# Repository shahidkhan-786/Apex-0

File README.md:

# Apex-0

Hello
This Readme is a detailed guide or can say walkthrough of my RC plane making journey.

Apex 0 is a RC trainer plane with 4 control channels.
Made with custom transmitter and reciever.
It will have four controls (Throttle, Ailerons, Rudder and Elevator) 
I will be using ESP32 along with ELRS for communication and controlling servos and throttle.

I am referring to this video : https://youtu.be/LzZ4Oqk_J1Y?si=26B0NShiXBWvZHp2
for structure part...but there was a flaw...The flight time...I have optimized the design for longer flight time.

Also I will be making my own remote controller with 2 Joystick modules.

Since I was little I was amazed by people flying planes and drones, basically all flying stuff. and thats why I wanna make my own plane.

Note that for the first iteration I will be making reciever on a perfboard/zero PCB ...and hence there is no pcb in 3D model.
Reviewers please do not overlook it.

so for the dimensions and proportions you can see my blueprints part where I have showed exact dimensions I will be using.

and for the 3D model you can see my 3D section.

Now for the electronics part :

The transmitter Circuit and PCB : 

and now the reciever part, again note that I am making this on a perfboard and hence there is no layout/routing part :

The BOM screenshots : 

Cart Screenshot (I am ordering froma website called Robu.in) :

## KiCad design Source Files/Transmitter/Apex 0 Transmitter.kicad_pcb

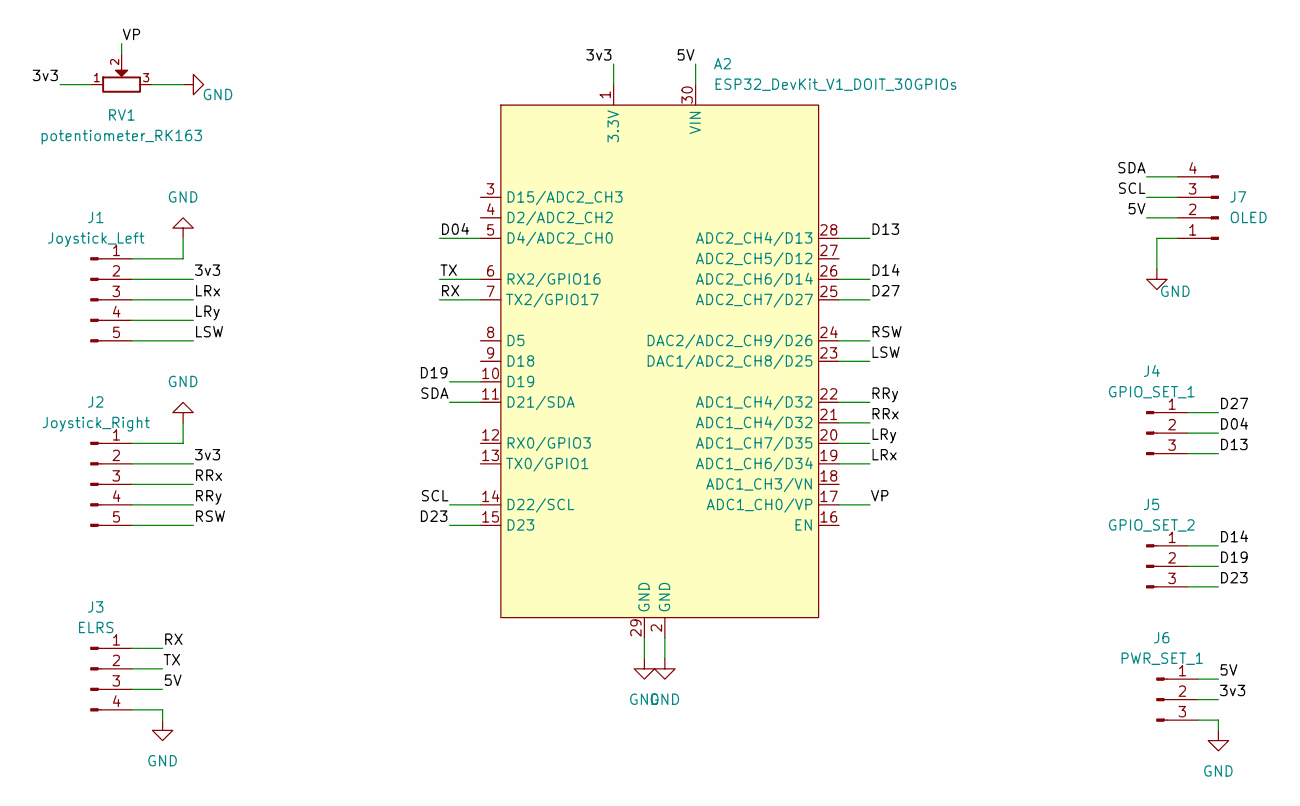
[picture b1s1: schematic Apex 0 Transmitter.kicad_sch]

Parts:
A2: ESP32_DevKit_V1_DOIT_30GPIOs; DOIT_ESP32_DEVKIT_30Pins
J1: Joystick_Left; PinHeader_1x05_P2.54mm_Vertical
J2: Joystick_Right; PinHeader_1x05_P2.54mm_Vertical
J3: ELRS; PinHeader_1x04_P2.54mm_Vertical
J4: GPIO_SET_1; PinHeader_1x03_P2.54mm_Vertical
J5: GPIO_SET_2; PinHeader_1x03_P2.54mm_Vertical
J6: PWR_SET_1; PinHeader_1x03_P2.54mm_Vertical
J7: OLED; PinHeader_1x04_P2.54mm_Vertical
RV1: potentiometer_RK163; Potentiometer_Alps_RK163_Single_Horizontal

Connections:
/3v3: A2.1 (3.3V), J1.2, J2.2, J6.2, RV1.1
/5V: A2.30 (VIN), J3.3, J6.1, J7.2
/D04: A2.5 (D4/ADC2_CH0), J4.2
/D13: A2.28 (ADC2_CH4/D13), J4.3
/D14: A2.26 (ADC2_CH6/D14), J5.1
/D19: A2.10 (D19), J5.2
/D23: A2.15 (D23), J5.3
/D27: A2.25 (ADC2_CH7/D27), J4.1
/LRx: A2.19 (ADC1_CH6/D34), J1.3
/LRy: A2.20 (ADC1_CH7/D35), J1.4
/LSW: A2.23 (DAC1/ADC2_CH8/D25), J1.5
/RRx: A2.21 (ADC1_CH4/D32), J2.3
/RRy: A2.22 (ADC1_CH4/D32), J2.4
/RSW: A2.24 (DAC2/ADC2_CH9/D26), J2.5
/RX: A2.7 (TX2/GPIO17), J3.1
/SCL: A2.14 (D22/SCL), J7.3
/SDA: A2.11 (D21/SDA), J7.4
/TX: A2.6 (RX2/GPIO16), J3.2
/VP: A2.17 (ADC1_CH0/VP), RV1.2
GND: A2.2 (GND), A2.29 (GND), J1.1, J2.1, J3.4, J6.3, J7.1, RV1.3

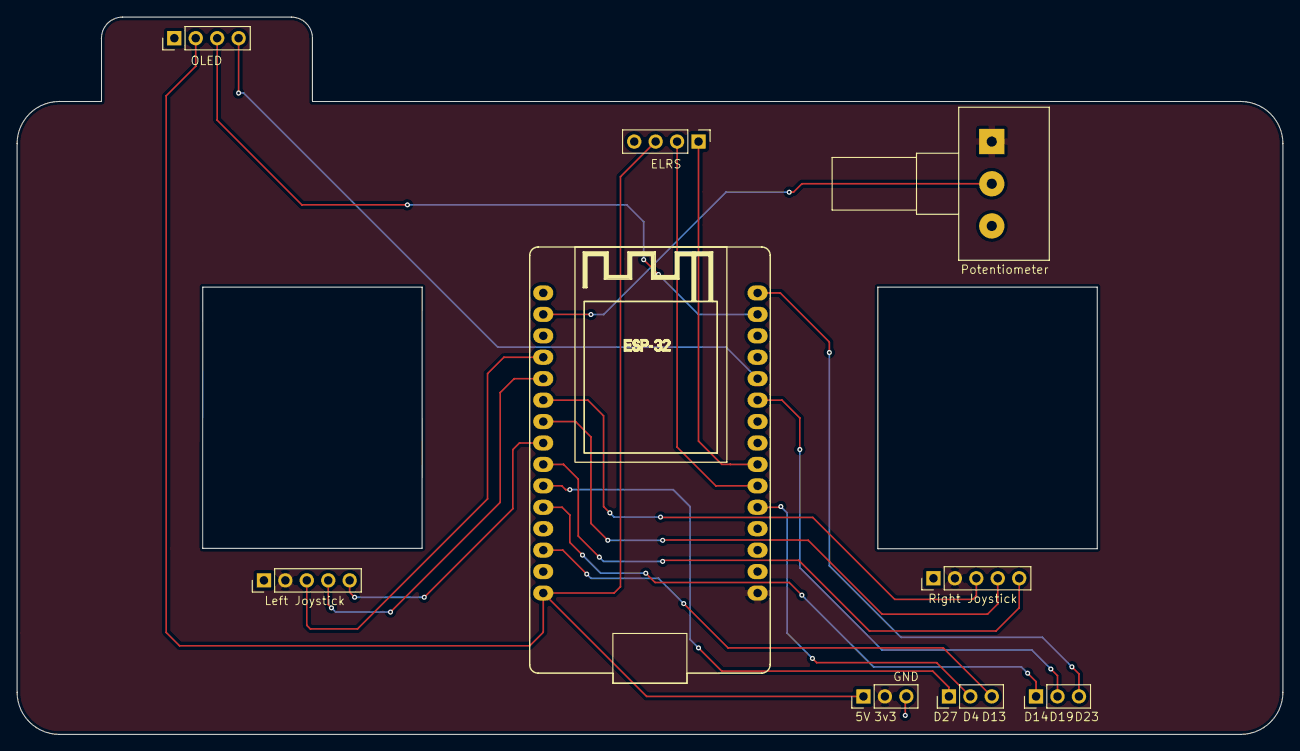
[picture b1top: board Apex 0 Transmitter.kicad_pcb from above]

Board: 2 copper layers, 150.0 x 85.0 mm, 9 parts (0 on the bottom side), 20 nets.

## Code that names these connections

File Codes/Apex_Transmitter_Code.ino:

/*
 * APEX 0 - DIY ExpressLRS Radio Transmitter Handset
 * Developed for Hack Club Macondo Project
 * * Target MCU: ESP32 30-Pin DevKit
 * Mappings perfectly matched to Final Transmitter Schematic
 */

#include <Wire.h>
#include <Adafruit_GFX.h>
#include <Adafruit_SSD1306.h>

// --- Hardware Pin Definitions ---
#define PIN_JOY_LEFT_X  34  // LRx (ADC1)
#define PIN_JOY_LEFT_Y  35  // LRy (ADC1)
#define PIN_SWITCH_LEFT 25  // LSW (Digital Input)

#define PIN_JOY_RIGHT_X 32  // RRx (ADC1)
#define PIN_JOY_RIGHT_Y 33  // RRy (ADC1)
#define PIN_SWITCH_RIGHT 26 // RSW (Digital Input)

#define PIN_POT_AUX     36  // VP (ADC1 Tuning Potentiometer)

#define PIN_UART_TX2    17  // Connected to ELRS RX Pad
#define PIN_UART_RX2    16  // Connected to ELRS TX Pad

// --- OLED Configuration ---
#define SCREEN_WIDTH 128
#define SCREEN_HEIGHT 64
Adafruit_SSD1306 display(SCREEN_WIDTH, SCREEN_HEIGHT, &Wire, -1);

// --- CRSF Frame Structures ---
#define CRSF_START_BYTE     0xC8
#define CRSF_FRAMETYPE_RC_CHANNELS 0x16

struct CrsfChannels {
    unsigned int ch0 : 11;
    unsigned int ch1 : 11;
    unsigned int ch2 : 11;
    unsigned int ch3 : 11;
    unsigned int ch4 : 11;
    unsigned int ch5 : 11;
    unsigned int ch6 : 11;
    unsigned int ch7 : 11;
    unsigned int ch8 : 11;
    unsigned int ch9 : 11;
    unsigned int ch10 : 11;
    unsigned int ch11 : 11;
    unsigned int ch12 : 11;
    unsigned int ch13 : 11;
    unsigned int ch14 : 11;
    unsigned int ch15 : 11;
} __attribute__((packed));

uint8_t crsfPacket[26];

// --- CRC8 Calculation Function for ExpressLRS ---
uint8_t crsf_crc8(const uint8_t *ptr, uint8_t len) {
    uint8_t crc = 0;
    while (len--) {
        crc ^= *ptr++;
        for (uint8_t i = 0; i < 8; i++) {
            if (crc & 0x80) {
                crc = (crc << 1) ^ 0xD5;
            } else {
                crc <<= 1;
            }
        }
    }
    return crc;
}

void setup() {
    // Initialize Debug Console
    Serial.begin(115200);
    
    // Initialize Hardware UART2 for ExpressLRS Module at native CRSF Speed
    Serial2.begin(416666, SERIAL_8N1, PIN_UART_RX2, PIN_UART_TX2);
    
    // Configure Switches with internal pullups
    pinMode(PIN_SWITCH_LEFT, INPUT_PULLUP);
    pinMode(PIN_SWITCH_RIGHT, INPUT_PULLUP);
    
    // Initialize I2C OLED Screen
    if(!display.begin(SSD1306_SWITCHCAPVCC, 0x3C)) {
        Serial.println(F("OLED allocation failed"));
    } else {
        display.clearDisplay();
        display.setTextSize(1);
        display.setTextColor(SSD1306_WHITE);
        display.setCursor(0,0);
        display.println("  APEX 0 TX ONLINE  ");
        display.println("   HACKCLUB MACONDO ");
        display.display();
    }
}

void loop() {
    // 1. Read Analog Joysticks and Pot (ESP32 12-bit ADC: 0 to 4095)
    int raw_roll     = analogRead(PIN_JOY_RIGHT_X);
    int raw_pitch    = analogRead(PIN_JOY_RIGHT_Y);
    int raw_throttle = analogRead(PIN_JOY_LEFT_Y);
    int raw_yaw      = analogRead(PIN_JOY_LEFT_X);
    int raw_aux      = analogRead(PIN_POT_AUX);
    
    // 2. Map values to standard ExpressLRS channel limits (CRSF ranges from 172 to 1811)
    // Center point is 992. Equivalent to standard 1000us - 2000us servo signals.
    uint16_t crsf_roll     = map(raw_roll,     0, 4095, 172, 1811);
    uint16_t crsf_pitch    = map(raw_pitch,    0, 4095, 172, 1811);
    uint16_t crsf_throttle = map(raw_throttle, 0, 4095, 172, 1811);
    uint16_t crsf_yaw      = map(raw_yaw,      0, 4095, 172, 1811);
    uint16_t crsf_aux      = map(raw_aux,      0, 4095, 172, 1811);
    
    uint16_t sw_l = (digitalRead(PIN_SWITCH_LEFT) == LOW) ? 1811 : 172;
    uint16_t sw_r = (digitalRead(PIN_SWITCH_RIGHT) == LOW) ? 1811 : 172;

    // 3. Assemble the CRSF Serialization Packet Array
    crsfPacket[0] = CRSF_START_BYTE;
    crsfPacket[1] = 24; // Packet Payload Length
    crsfPacket[2] = CRSF_FRAMETYPE_RC_CHANNELS;
    
    CrsfChannels *channels = (CrsfChannels *)&crsfPacket[3];
    channels->ch0 = crsf_roll;
    channels->ch1 = crsf_pitch;
    channels->ch2 = crsf_throttle;
    channels->ch3 = crsf_yaw;
    channels->ch4 = sw_l;
    channels->ch5 = sw_r;
    channels->ch6 = crsf_aux;
    
    // Calculate Checksum over payload and payload header type
    crsfPacket[25] = crsf_crc8(&crsfPacket[2], 23);
    
    // 4. Stream data frame down the serial pipeline directly to the ELRS module
    Serial2.write(crsfPacket, 26);
    
    // 5. Refresh OLED Telemetry Screen Layout at a clean 10Hz pace
    static unsigned long lastUpdate = 0;
    if (millis() - lastUpdate > 100) {
        lastUpdate = millis();
        display.clearDisplay();
        display.setCursor(0,0);
        display.println("--- APEX 0 LINK ---");
        display.printf("THR: %d\n", map(crsf_throttle, 172, 1811, 0, 100));
        display.printf("RLL: %d | PTH: %d\n", map(crsf_roll, 172, 1811, -50, 50), map(crsf_pitch, 172, 1811, -50, 50));
        display.printf("AUX POT: %d\n", map(crsf_aux, 172, 1811, 0, 100));
        display.println("STATUS: WAITING RX...");
        display.display();
    }
    
    delay(20); // Balanced 50Hz control loop interval
}

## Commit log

2026-02-22 Update README with Trainer plane project details
    Added details about the Trainer plane project and its components.
2026-02-22 Create Apex 0
2026-02-22 These are Cart Screenshots
2026-02-22 Main Blueprint
    These are the main Schematic I will be using for the build.
2026-02-22 Add files via upload
    This is screenshot of my BOM
2026-03-22 Create Apex-0
    This folder contains all 3D files and also Screenshoots required
2026-03-22 These are the 3D files required
    These are Rough (Yet most finished) models...you have to place holes according to your screw needs and also motor mounts according to your motor sizes.
    I have made the sketch in Blueprint folder where can you place motor mounts according to your motor and needs
2026-03-23 Update README with project details and image
    Added an image and additional information about the project.
2026-03-23 Update README with 3D model section and images
    Removed redundancy in the 3D model section and added additional screenshots.
2026-03-23 Update README with new images
    Added additional images to the README for better visualization.
2026-03-24 Add transmitter code for RF24 communication
2026-03-24 Add receiver code for RF24 radio and servos
2026-03-24 Add note about ESP32 version differences
2026-03-25 This is BOM for the project
2026-03-25 Update README with Bill of Materials and images
    Added Bill of Materials section and updated images.
2026-05-08 Justification for 12Hrs
    Unfortunately I can't show each and every parametric of model/sketches...but seeing the timeline you know that I have genuinely put hours in making...
2026-05-18 Revise README for Apex 0 RC plane project
    Updated the README to enhance clarity and detail about the RC plane project, including transmitter and receiver schematics.
2026-05-21 Update README with notes on circuit design and PCB
    Added a note about using perfboard for the first iteration and clarified the absence of a PCB in the 3D model.
2026-05-31 Add project transfer notes for material
    Document project transfer history and reasons.
2026-05-31 Add project notes about transfer history
2026-05-31 Screenshot of Blueprint reviewer note
    Hope it helps to review faster
2026-06-01 Update project transfer notes
    Expanded project notes regarding transfers and AI usage.
2026-06-03 Update Note
2026-06-03 Update project notes with transfer and funding details
    Added details about project transfer and AI usage.
2026-06-17 Update README for communication method and receiver details
2026-06-17 Update Important note
2026-06-17 Create Reciever
2026-06-17 Create Source Files
2026-06-17 Cart Screenshot
2026-06-17 BOM Screenshot
2026-06-17 Enhance README with project motivation and images
    Added personal motivation and details about the project, including the BOM and cart screenshots.
2026-06-17 Update project note with additional details
    Added details about project complexity and funding plans.
2026-06-18 Update BOM with new items and totals
2026-06-27 Transmitter Gerber
2026-06-28 Expand instructions for foam board plane assembly
    Added detailed instructions for assembling a foam board model plane, including cutting, joining parts, servo attachment, hinge creation, and placement of components.
2026-06-28 Fix BOM screenshot reference and add new images
    Updated the README to correct the BOM screenshot reference and added additional screenshots.
